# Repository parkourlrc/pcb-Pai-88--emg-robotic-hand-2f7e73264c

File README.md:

# EMG-Controlled Robotic Hand

A wearable single-channel surface-EMG front end that reads how hard a forearm
muscle contracts and drives a robotic gripper proportionally. The whole control
loop runs on a Raspberry Pi Pico rather than on a PC: squeeze harder and the
grip closes further, relax and it opens.

> ### Safety: read this before building anything
>
> This is an experimental, self-built device that puts electrodes on skin. It
> is not a medical device, has not been certified, and must not be used for
> diagnosis, monitoring, or any clinical purpose.
>
> - **Battery power only.** Never wear the electrodes while anything in the
>   signal path is connected to mains. The driven-right-leg (DRL) circuit
>   actively drives the reference electrode; R14 (390 kΩ) holds body current
>   under 5 µA, but that only holds while the board is isolated from mains.
>   Powering the Pico from a laptop that is plugged in to charge defeats it, so
>   run the host on its own battery whenever electrodes are on skin.
> - The board carries the silkscreen legend **"BATTERY POWER ONLY - no mains
>   while worn"** and has no provision for a mains adapter.
> - Build and use it at your own risk.

## Status

The rev E board is built and the digital side works on real hardware. The
analog front end has not been powered yet, so no EMG has been recorded from
skin. What has been checked so far:

| Part | State |
|---|---|
| Analog front end (rev E) | Designed, DRC-clean, fabricated at JLCPCB and hand-soldered. Servo section (J5-J9, J10, C8) left unpopulated. C3 not fitted yet. The +/-9 V rails are not connected, so the front end itself is unverified |
| Firmware logic | 77 native tests pass (DSP, safety FSM, control law, protocol) |
| Firmware on hardware | Builds with PlatformIO, flashed to the Pico, enumerates over USB |
| Telemetry link (bring-up gate 4) | Passes. 10 s capture: 499 frames at 49.87 frames/s, 997.4 Hz sample rate, 0 CRC errors, 0 dropped frames, 0 resyncs |
| Host tools | Python test suite passes against a simulator, and `host.cli monitor` runs against the real board |
| On-body EMG | Not done. Next steps are in [`board/revd/bringup.md`](board/revd/bringup.md): connect +/-9 V (check polarity first), check rails and VMID, fit C3, then stage 5 on battery |

A few fitted resistors differ from the schematic because I did not have the
exact values (R5 = 10k, R6 = 3.3k, R11 = R12 = 100k, R13 = 3.3M, R14 = 470k).
Total gain is about 227 instead of the designed 336. Anything not listed as
passing above should be treated as unverified.

## How it works

```
electrode (forearm)                        Raspberry Pi Pico (RP2040)
   │  ~a few hundred µV                        │
   ▼                                           ▼
AD623 in-amp  ─►  MCP6004 gain + 442 Hz LPF ─► ADC0 @ 1 kHz ─► 20 Hz HPF,
   (×20.6)          (×16, total ≈ 330)         │               50/100/150 Hz notches,
                                               │               rectify + 200 ms RMS envelope
   driven-right-leg mains rejection            │
                                               ▼
                                        safety state machine ─► proportional
                                        (INIT/IDLE/ACTIVE/HOLD/                map + slew limit
                                         FAULT/latched ESTOP)                       │
                                                                                    ▼
                                                                            servo PWM ─► geared gripper
```

- The control loop runs entirely on the Pico. The host (a Mac or a Pi 5 over
  USB) only plots, calibrates, and logs, so if you unplug it the gripper keeps
  working.
- One EMG channel measures how hard the muscle is working, not which hand
  posture you are making. Contraction strength maps continuously onto grip
  aperture, which suits a one-degree-of-freedom gripper. There is no gesture
  classifier, no training data, and no ML model to run at runtime. (More in
  [`firmware/pico_emg/README.md`](firmware/pico_emg/README.md).)
- There are no force sensors on the board, so the firmware uses signal quality
  itself as a safety check: it watches for saturation, flat-line, DC drift, and
  stale data, and releases the grip on a sustained fault instead of freezing it.

Key numbers: about 330× total gain, 2.443 µV per ADC count referred to skin,
1 kHz sampling, 442 Hz single-pole anti-alias, DRL mains rejection, and a
100 × 100 mm 2-layer through-hole board.

## Hardware

The analog front end is a single KiCad project (rev E). Full sources, exported
gerbers, and fab notes are under [`board/revd/`](board/revd/).

**Schematic.** Two-stage gain, driven-right-leg mains rejection, VMID
reference, ADC clamp protection, and the isolated servo-output block:

**PCB.** 100 x 100 mm, 2-layer, all through-hole:

## Repository layout

| Path | What |
|---|---|
| [`board/revd/`](board/revd/) | The rev E analog front end: KiCad sources, exported gerbers, and the [`constraints`](board/revd/constraints.md) / [`fab`](board/revd/fab.md) / [`bringup`](board/revd/bringup.md) docs. (The directory is named `revd` for historical reasons; the board it holds is rev E.) |
| [`firmware/pico_emg/`](firmware/pico_emg/) | RP2040 firmware: header-only DSP, safety FSM, control law, PICO1 telemetry, and 77 native logic tests |
| [`host/`](host/) | USB observer (plot / calibrate / log), deliberately not in the control loop |
| [`tests/`](tests/) | Host-side tests, including wire-format parity against the firmware |
| [`docs/wiring/`](docs/wiring/) | LaTeX wiring / connection guide |

*The 3D-printable gripper CAD is being reworked and will be added in a later
update.*

## Build & test

```bash
# Firmware: Raspberry Pi Pico / RP2040 (PlatformIO)
cd firmware/pico_emg
pio run -e pico            # builds firmware.uf2
./test/run_tests.sh        # 77 native logic tests (compiles the real headers)

# Host tools: Python, from the repo root
python3 -m pytest                        # host test suite
python3 -m host.cli selftest             # no hardware needed
python3 -m host.cli --simulate monitor   # run the pipeline against simulated EMG
```

## Bring-up

If you fabricate the board, work through
[`board/revd/bringup.md`](board/revd/bringup.md) top to bottom and do not skip a
failed gate. Several stages put voltage near skin, and stages 4–6 need the host
running on battery, unplugged from mains. Only when every gate passes with real
numbers should any part of this be described as working.

## License

[MIT](LICENSE) © 2026 Paing Hein Htet.

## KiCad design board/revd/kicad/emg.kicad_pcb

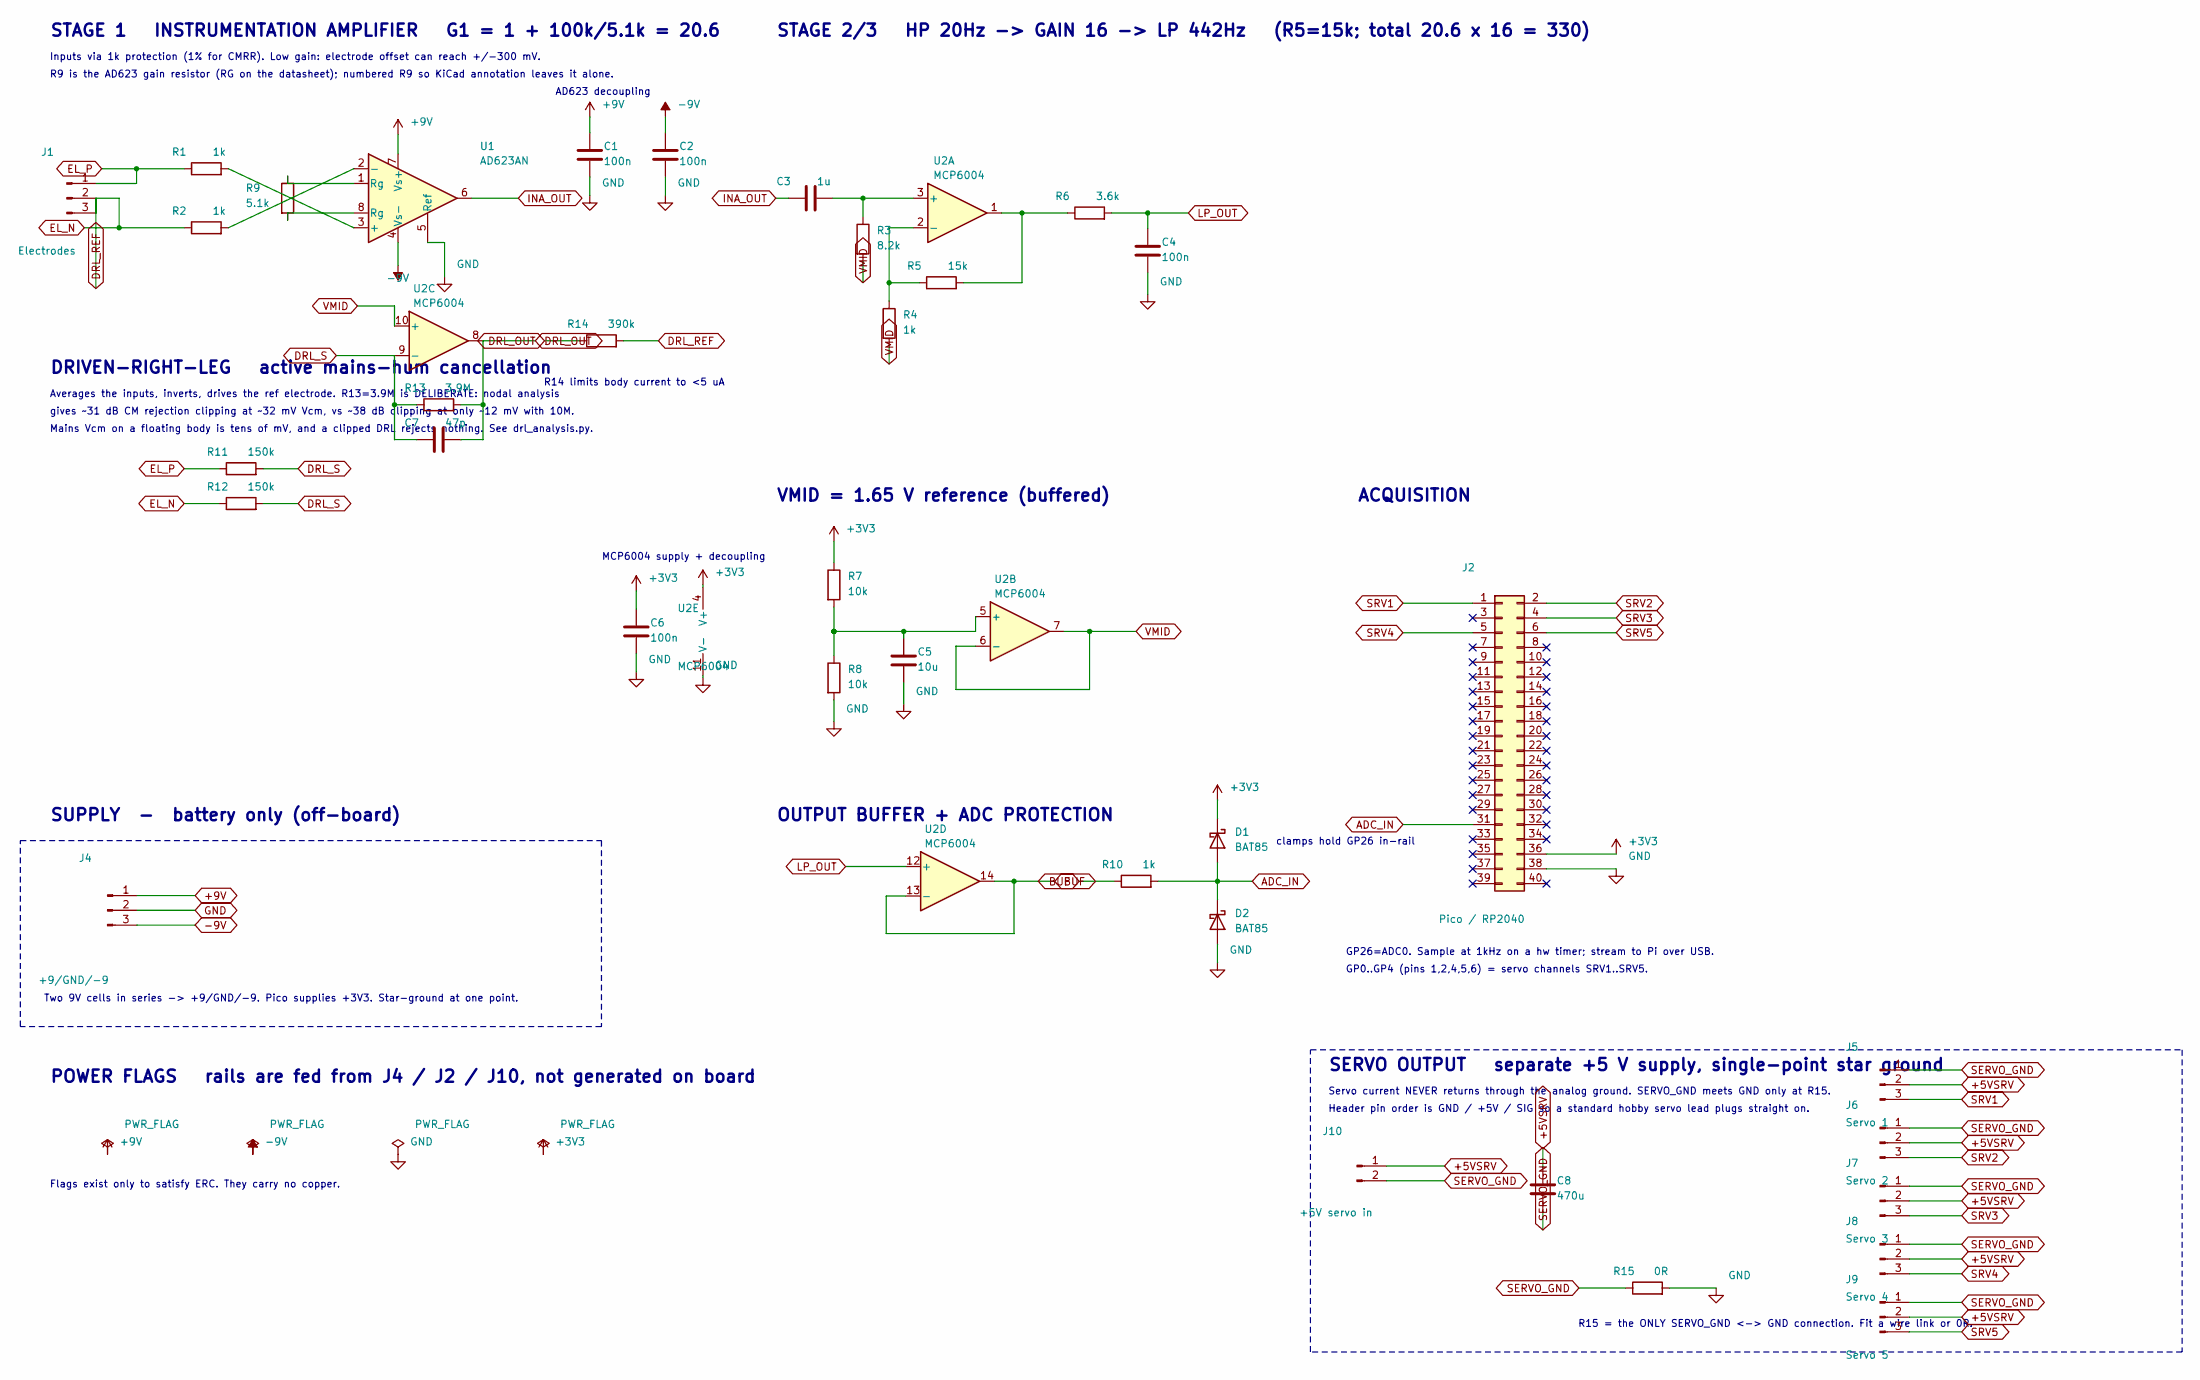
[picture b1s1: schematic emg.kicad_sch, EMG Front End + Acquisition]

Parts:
C1, C2, C4, C6: 100n; C_Disc_D5.0mm_W2.5mm_P5.00mm
C3: 1u; C_Rect_L7.0mm_W2.0mm_P5.00mm
C5: 10u; CP_Radial_D5.0mm_P2.50mm
C7: 47p; C_Disc_D5.0mm_W2.5mm_P5.00mm
C8: 470u; CP_Radial_D10.0mm_P5.00mm
D1, D2: BAT85; D_DO-35_SOD27_P7.62mm_Horizontal
J1: Electrodes; PinHeader_1x03_P2.54mm_Vertical
J2: Pico / RP2040; Pico_Socket_2x1x20
J4: +9/GND/-9; TerminalBlock_Phoenix_MPT-0,5-3-2.54_1x03_P2.54mm_Horizontal
J5: Servo 1; PinHeader_1x03_P2.54mm_Vertical
J6: Servo 2; PinHeader_1x03_P2.54mm_Vertical
J7: Servo 3; PinHeader_1x03_P2.54mm_Vertical
J8: Servo 4; PinHeader_1x03_P2.54mm_Vertical
J9: Servo 5; PinHeader_1x03_P2.54mm_Vertical
J10: +5V servo in; TerminalBlock_Phoenix_MPT-0,5-2-2.54_1x02_P2.54mm_Horizontal
R1, R2, R4, R10: 1k; R_Axial_DIN0207_L6.3mm_D2.5mm_P10.16mm_Horizontal
R3: 8.2k; R_Axial_DIN0207_L6.3mm_D2.5mm_P10.16mm_Horizontal
R5: 15k; R_Axial_DIN0207_L6.3mm_D2.5mm_P10.16mm_Horizontal
R6: 3.6k; R_Axial_DIN0207_L6.3mm_D2.5mm_P10.16mm_Horizontal
R7, R8: 10k; R_Axial_DIN0207_L6.3mm_D2.5mm_P10.16mm_Horizontal
R9: 5.1k; R_Axial_DIN0207_L6.3mm_D2.5mm_P10.16mm_Horizontal
R11, R12: 150k; R_Axial_DIN0207_L6.3mm_D2.5mm_P10.16mm_Horizontal
R13: 3.9M; R_Axial_DIN0207_L6.3mm_D2.5mm_P10.16mm_Horizontal
R14: 390k; R_Axial_DIN0207_L6.3mm_D2.5mm_P10.16mm_Horizontal
R15: 0R; R_Axial_DIN0207_L6.3mm_D2.5mm_P10.16mm_Horizontal
U1: AD623AN; DIP-8_W7.62mm
U2: MCP6004; DIP-14_W7.62mm

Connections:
+3V3: C6.1, D1.1 (K), J2.36, R7.1, U2.4 (V+)
+5VSRV: C8.1, J5.2, J6.2, J7.2, J8.2, J9.2, J10.1
+9V: C1.1, J4.1, U1.7 (Vs+)
-9V: C2.1, J4.3, U1.4 (Vs-)
ADC_IN: D1.2 (A), D2.1 (K), J2.31, R10.2
BUF: R10.1, U2.13 (-), U2.14
DRL_OUT: C7.2, R13.2, R14.1, U2.8
DRL_REF: J1.3, R14.2
DRL_S: C7.1, R11.2, R12.2, R13.1, U2.9 (-)
EL_N: J1.2, R2.1, R12.1
EL_P: J1.1, R1.1, R11.1
GND: C1.2, C2.2, C4.2, C5.2, C6.2, D2.2 (A), J2.38, J4.2, R8.2, R15.2, U1.5 (Ref), U2.11 (V-)
INA_OUT: C3.1, U1.6
LP_OUT: C4.1, R6.2, U2.12 (+)
unnamed: R5.2, R6.1, U2.1
unnamed: R9.1, U1.1 (Rg)
unnamed: R9.2, U1.8 (Rg)
unnamed: R1.2, U1.3 (+)
unnamed: R2.2, U1.2 (-)
unnamed: C3.2, R3.1, U2.3 (+)
unnamed: R4.1, R5.1, U2.2 (-)
unnamed: C5.1, R7.2, R8.1, U2.5 (+)
SERVO_GND: C8.2, J5.1, J6.1, J7.1, J8.1, J9.1, J10.2, R15.1
SRV1: J2.1, J5.3
SRV2: J2.2, J6.3
SRV3: J2.4, J7.3
SRV4: J2.5, J8.3
SRV5: J2.6, J9.3
VMID: R3.2, R4.2, U2.6 (-), U2.7, U2.10 (+)

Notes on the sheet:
STAGE 1 INSTRUMENTATION AMPLIFIER G1 = 1 + 100k/5.1k = 20.6
Inputs via 1k protection (1% for CMRR). Low gain: electrode offset can reach +/-300 mV.
R9 is the AD623 gain resistor (RG on the datasheet); numbered R9 so KiCad annotation leaves it alone.
AD623 decoupling
DRIVEN-RIGHT-LEG active mains-hum cancellation
Averages the inputs, inverts, drives the ref electrode. R13=3.9M is DELIBERATE: nodal analysis
gives ~31 dB CM rejection clipping at ~32 mV Vcm, vs ~38 dB clipping at only ~12 mV with 10M.
Mains Vcm on a floating body is tens of mV, and a clipped DRL rejects nothing. See drl_analysis.py.
R14 limits body current to <5 uA
STAGE 2/3 HP 20Hz -> GAIN 16 -> LP 442Hz (R5=15k; total 20.6 x 16 = 330)
VMID = 1.65 V reference (buffered)
OUTPUT BUFFER + ADC PROTECTION
clamps hold GP26 in-rail
MCP6004 supply + decoupling
SUPPLY - battery only (off-board)
Two 9V cells in series -> +9/GND/-9. Pico supplies +3V3. Star-ground at one point.
ACQUISITION
GP26=ADC0. Sample at 1kHz on a hw timer; stream to Pi over USB.
GP0..GP4 (pins 1,2,4,5,6) = servo channels SRV1..SRV5.
SERVO OUTPUT separate +5 V supply, single-point star ground
Servo current NEVER returns through the analog ground. SERVO_GND meets GND only at R15.
Header pin order is GND / +5V / SIG so a standard hobby servo lead plugs straight on.
R15 = the ONLY SERVO_GND <-> GND connection. Fit a wire link or 0R.
POWER FLAGS rails are fed from J4 / J2 / J10, not generated on board
Flags exist only to satisfy ERC. They carry no copper.

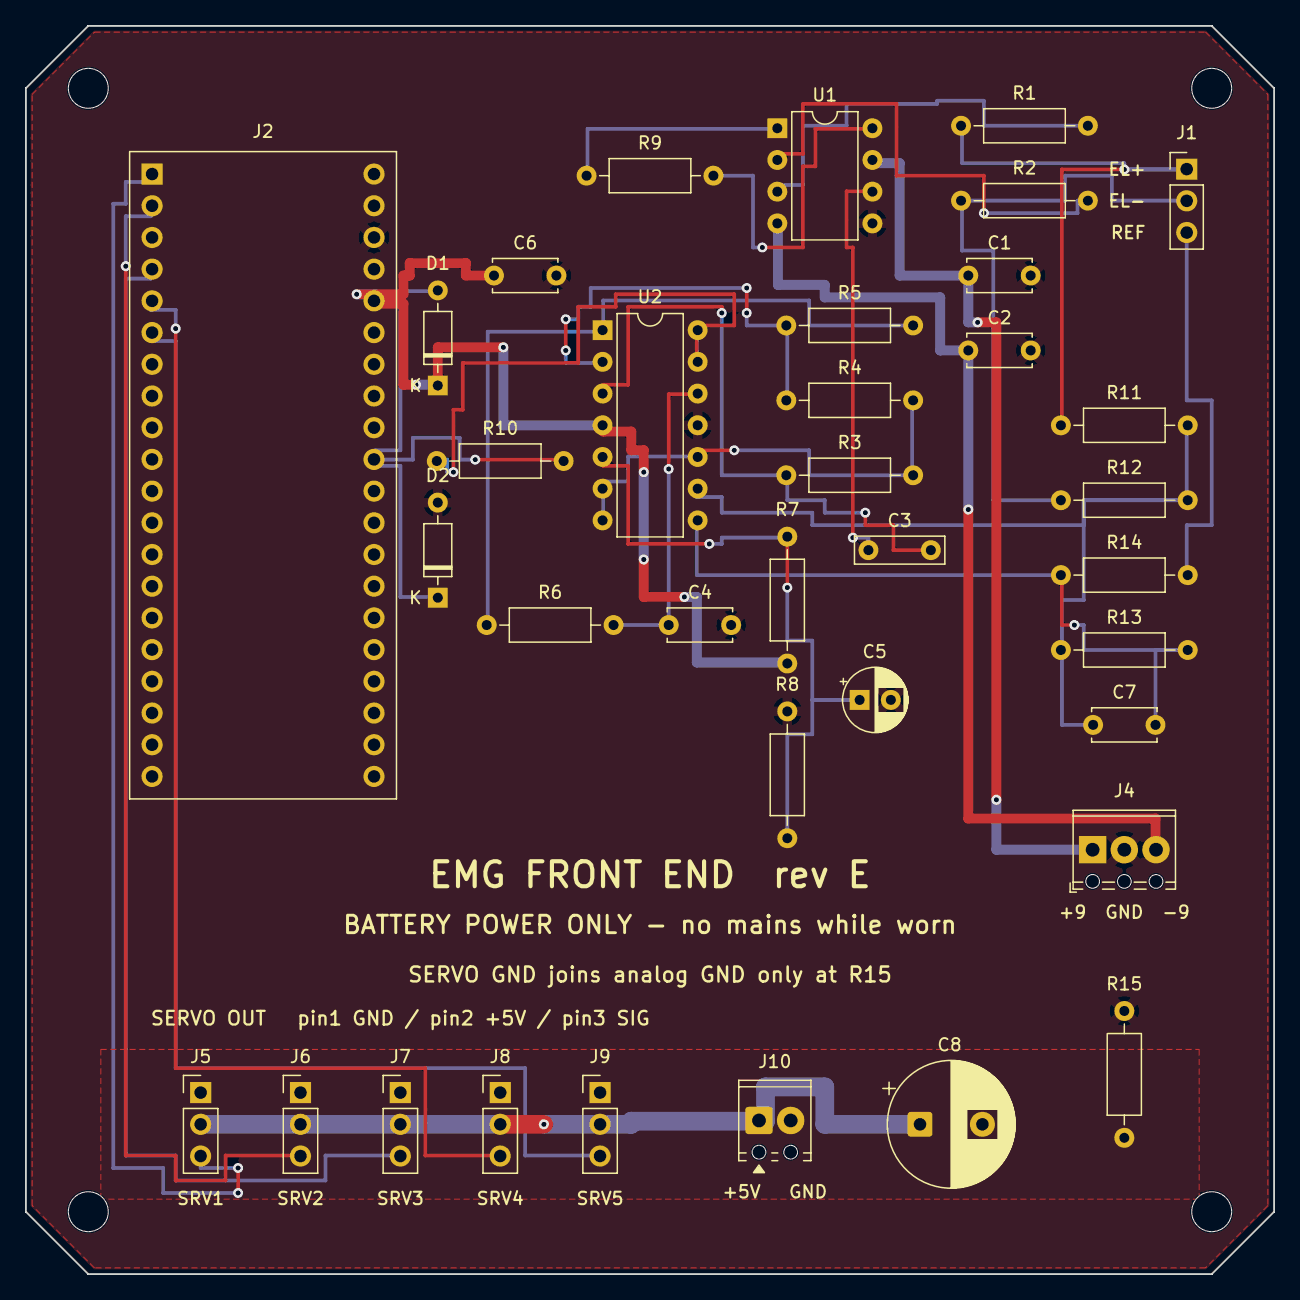
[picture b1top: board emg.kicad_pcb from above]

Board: 2 copper layers, 100.0 x 100.0 mm, 40 parts (0 on the bottom side), 29 nets.

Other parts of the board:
H1, H2, H3, H4: MountingHole_3.2mm_M3

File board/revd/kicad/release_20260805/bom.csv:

"Refs","Value","Footprint","Qty"
"C1,C2,C4,C6","100n","Capacitor_THT:C_Disc_D5.0mm_W2.5mm_P5.00mm","4"
"C3","1u","Capacitor_THT:C_Rect_L7.0mm_W2.0mm_P5.00mm","1"
"C5","10u","Capacitor_THT:CP_Radial_D5.0mm_P2.50mm","1"
"C7","47p","Capacitor_THT:C_Disc_D5.0mm_W2.5mm_P5.00mm","1"
"C8","470u","Capacitor_THT:CP_Radial_D10.0mm_P5.00mm","1"
"D1,D2","BAT85","Diode_THT:D_DO-35_SOD27_P7.62mm_Horizontal","2"
"J1","Electrodes","Connector_PinHeader_2.54mm:PinHeader_1x03_P2.54mm_Vertical","1"
"J2","Pico / RP2040","emg:Pico_Socket_2x1x20","1"
"J4","+9/GND/-9","TerminalBlock_Phoenix:TerminalBlock_Phoenix_MPT-0,5-3-2.54_1x03_P2.54mm_Horizontal","1"
"J5","Servo 1","Connector_PinHeader_2.54mm:PinHeader_1x03_P2.54mm_Vertical","1"
"J6","Servo 2","Connector_PinHeader_2.54mm:PinHeader_1x03_P2.54mm_Vertical","1"
"J7","Servo 3","Connector_PinHeader_2.54mm:PinHeader_1x03_P2.54mm_Vertical","1"
"J8","Servo 4","Connector_PinHeader_2.54mm:PinHeader_1x03_P2.54mm_Vertical","1"
"J9","Servo 5","Connector_PinHeader_2.54mm:PinHeader_1x03_P2.54mm_Vertical","1"
"J10","+5V servo in","TerminalBlock_Phoenix:TerminalBlock_Phoenix_MPT-0,5-2-2.54_1x02_P2.54mm_Horizontal","1"
"R1,R2,R4,R10","1k","Resistor_THT:R_Axial_DIN0207_L6.3mm_D2.5mm_P10.16mm_Horizontal","4"
"R3","8.2k","Resistor_THT:R_Axial_DIN0207_L6.3mm_D2.5mm_P10.16mm_Horizontal","1"
"R5","15k","Resistor_THT:R_Axial_DIN0207_L6.3mm_D2.5mm_P10.16mm_Horizontal","1"
"R6","3.6k","Resistor_THT:R_Axial_DIN0207_L6.3mm_D2.5mm_P10.16mm_Horizontal","1"
"R7,R8","10k","Resistor_THT:R_Axial_DIN0207_L6.3mm_D2.5mm_P10.16mm_Horizontal","2"
"R9","5.1k","Resistor_THT:R_Axial_DIN0207_L6.3mm_D2.5mm_P10.16mm_Horizontal","1"
"R11,R12","150k","Resistor_THT:R_Axial_DIN0207_L6.3mm_D2.5mm_P10.16mm_Horizontal","2"
"R13","3.9M","Resistor_THT:R_Axial_DIN0207_L6.3mm_D2.5mm_P10.16mm_Horizontal","1"
"R14","390k","Resistor_THT:R_Axial_DIN0207_L6.3mm_D2.5mm_P10.16mm_Horizontal","1"
"R15","0R","Resistor_THT:R_Axial_DIN0207_L6.3mm_D2.5mm_P10.16mm_Horizontal","1"
"U1","AD623AN","Package_DIP:DIP-8_W7.62mm","1"
"U2","MCP6004","Package_DIP:DIP-14_W7.62mm","1"

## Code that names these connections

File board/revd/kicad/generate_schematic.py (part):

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lab_stub((40,92.38),"EL_P",-6); lab_stub((37,102.54),"EL_N",-6)
# reference electrode = J1.3, driven by the DRL amp (net DRL_REF). Drawn here at
# J1 so it travels with STAGE 1; the DRL block picks it up by net name.
s.wire(J1["3"],(33,B1),(33,113)); s.label((33,113),"DRL_REF",90,"left")
s.wire(U1["1"],(66,94.92),RG["1"]); s.wire(U1["8"],(66,100.0),RG["2"])
s.wire(U1["7"],(85,86.5)); s.power("+9V",(85,86.5))
s.wire(U1["4"],(85,109)); s.power("-9V",(85,109),down=True)
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            refpos=(87.5,113),valpos=(87.5,115.5),fp=FP_DIP14)
sIN, pIN, oUT = U2C["9"], U2C["10"], U2C["8"]
# +IN -> VMID (up and away)
s.wire(pIN,(pIN[0],116),(78,116)); s.label((78,116),"VMID",180,"right")
# -IN = summing node DRL_S
lab_stub((sIN[0],sIN[1]),"DRL_S",-10)
# feedback Rf + Cf below the amp
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# output -> safety R -> reference electrode
lab_stub(oUT,"DRL_OUT",9)
R14 = s.series("R14","390k",120,122,fp=FP_R)
s.wire(oUT,R14["1"]); s.junction(oUT)   # op-amp output wired straight into R14 (one DRL_OUT label)
s.wire(R14["2"],(R14["2"][0]+6,122)); s.label((R14["2"][0]+6,122),"DRL_REF",0,"left")
# (the reference electrode J1.3 is labelled DRL_REF over in the STAGE 1 block)
# averaging resistors EL_P/EL_N -> DRL_S
R11 = s.series("R11","150k",58,144,fp=FP_R)
lab_stub(R11["1"],"EL_P",-6); lab_stub(R11["2"],"DRL_S",6)
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s.at("stage23")
T(150,70,"STAGE 2/3  -  HPF -> x16 -> LPF 442 Hz")
C3 = s.series("C3","1u",156,B1,kind="C",fp=FP_C1U)
s.label((150,B1),"INA_OUT",180,"right"); s.wire((150,B1),C3["1"])
R3 = s.shunt("R3","8.2k",165,104.5,fp=FP_R)
s.wire(C3["2"],(173.62,B1)); s.junction((165,B1)); s.wire((165,B1),R3["1"])
s.wire(R3["2"],(165,112)); s.label((165,112),"VMID",270,"left")
U2A = s.sym("Amplifier_Operational","MCP6004","U2","MCP6004",(181.24,100),unit=1,
            refpos=(177,91),valpos=(177,93.5),fp=FP_DIP14)
s.wire((173.62,B1),U2A["3"])
s.wire(U2A["2"],(169.5,102.54),(169.5,112)); s.junction((169.5,112))
R4 = s.shunt("R4","1k",169.5,119,fp=FP_R)
s.wire((169.5,112),R4["1"]); s.wire(R4["2"],(169.5,126)); s.label((169.5,126),"VMID",270,"left")
R5 = s.series("R5","15k",178.5,112,fp=FP_R)
s.wire((169.5,112),R5["1"]); s.wire(R5["2"],(192.36,112),(192.36,100)); s.junction((192.36,100)); s.wire(U2A["1"],(192.36,100))
R6 = s.series("R6","3.6k",204,100,fp=FP_R)
s.wire((192.36,100),R6["1"])
C4 = s.shunt("C4","100n",214,106.5,kind="C",fp=FP_C)
s.wire(R6["2"],(221,100)); s.junction((214,100)); s.wire((214,100),C4["1"])
s.wire(C4["2"],(214,114)); s.power("GND",(214,114)); s.label((221,100),"LP_OUT")
s.box(143,63,232,135)

# ---------------------------------------------------------------- VMID buffer (U2B)
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T(150,205,"OUTPUT BUFFER + ADC PROTECTION")
U2D = s.sym("Amplifier_Operational","MCP6004","U2","MCP6004",(180,215),unit=4,
            refpos=(175.5,206),valpos=(175.5,208.5),fp=FP_DIP14)
s.wire(U2D["12"],(170,212.46)); s.label((162,212.46),"LP_OUT",180,"right"); s.wire((162,212.46),(170,212.46))
s.wire(U2D["13"],(169,217.54),(169,224),(191,224),(191,215)); s.junction((191,215)); s.wire(U2D["14"],(191,215))
R10 = s.series("R10","1k",212,215,fp=FP_R)
s.wire((191,215),R10["1"])   # buffer output wired straight into R10 (no redundant net label)
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s.wire(D1["1"],(226,201)); s.power("+3V3",(226,201)); s.wire(D1["2"],(226,215))
D2 = s.vdiode("D2","BAT85",226,222,fp=FP_D)
s.wire(D2["1"],(226,215)); s.wire(D2["2"],(226,229)); s.power("GND",(226,229))
s.label((232,215),"ADC_IN"); s.note((198,231),"BAT85 clamps keep GP26 in-rail",1.15)
s.box(148,199,250,234)

# ---------------------------------------------------------------- MCP6004 power (unit 5)
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    p=J2[num]; right=p[0]>275; end=(p[0]+(12 if right else -12),p[1]); s.wire(p,end)
    (s.power(kind,end) if kind else s.label(end,net,0 if right else 180,"left" if right else "right"))
s.note((248,228),"GP26=ADC0. Sample at 1kHz on a hw timer; stream to Pi over USB.",1.2)
s.note((248,231),"GP0..GP4 (pins 1,2,4,5,6) = servo channels SRV1..SRV5.",1.2)
# Mark every Pico pin we deliberately leave open, so a real floating input
# is never hidden among 32 routine 'pin not connected' messages. (Stays in this
# block so the no-connects travel with J2.)
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C8 = s.shunt("C8","470u",282,268,kind="C",
             fp="Capacitor_THT:CP_Radial_D10.0mm_P5.00mm")
s.wire(C8["1"],(282,261)); s.label((282,261),"+5VSRV",90,"left")
s.wire(C8["2"],(282,275)); s.label((282,275),"SERVO_GND",270,"left")

# the single star-ground link between the servo return and analog ground
R15 = s.series("R15","0R",272,285,fp=FP_R)
s.wire(R15["1"],(R15["1"][0]-8,285)); s.label((R15["1"][0]-8,285),"SERVO_GND",180,"right")
s.wire(R15["2"],(R15["2"][0]+8,285)); s.power("GND",(R15["2"][0]+8,285))
s.note((245,290),"R15 = only SERVO_GND-GND link; fit 0R or wire.",1.15)
s.note((245,293),"Servo header order: GND / +5V / SIG.",1.15)
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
